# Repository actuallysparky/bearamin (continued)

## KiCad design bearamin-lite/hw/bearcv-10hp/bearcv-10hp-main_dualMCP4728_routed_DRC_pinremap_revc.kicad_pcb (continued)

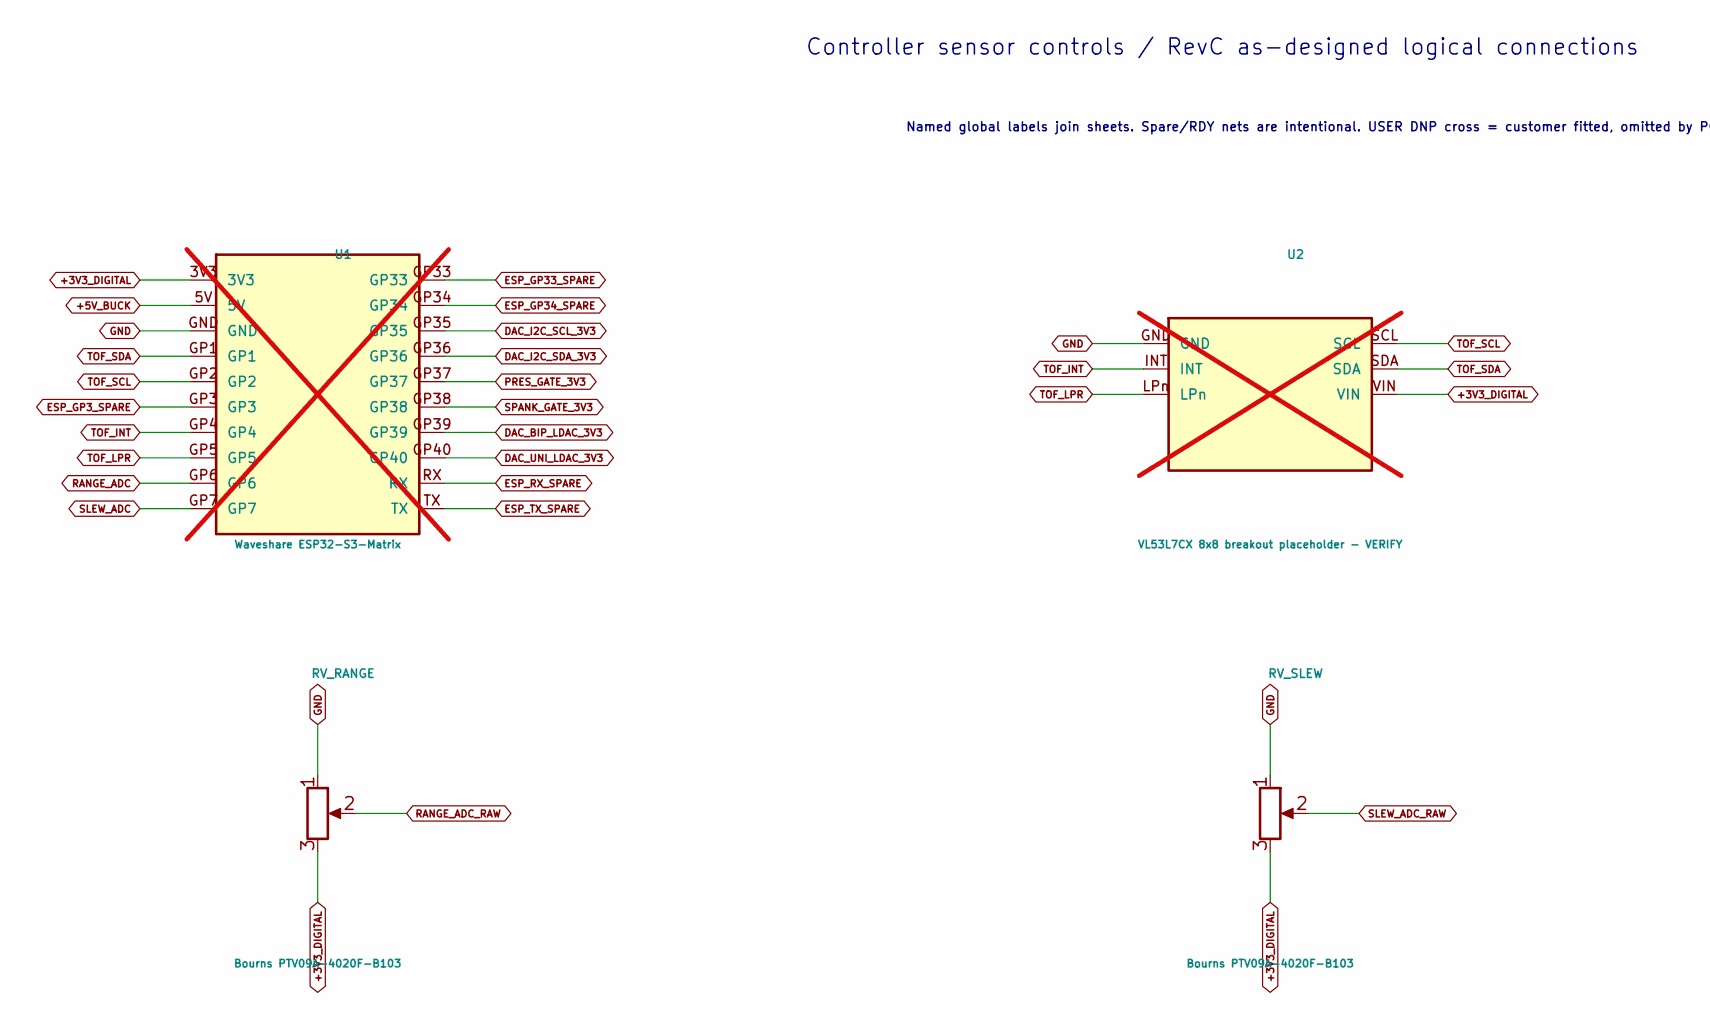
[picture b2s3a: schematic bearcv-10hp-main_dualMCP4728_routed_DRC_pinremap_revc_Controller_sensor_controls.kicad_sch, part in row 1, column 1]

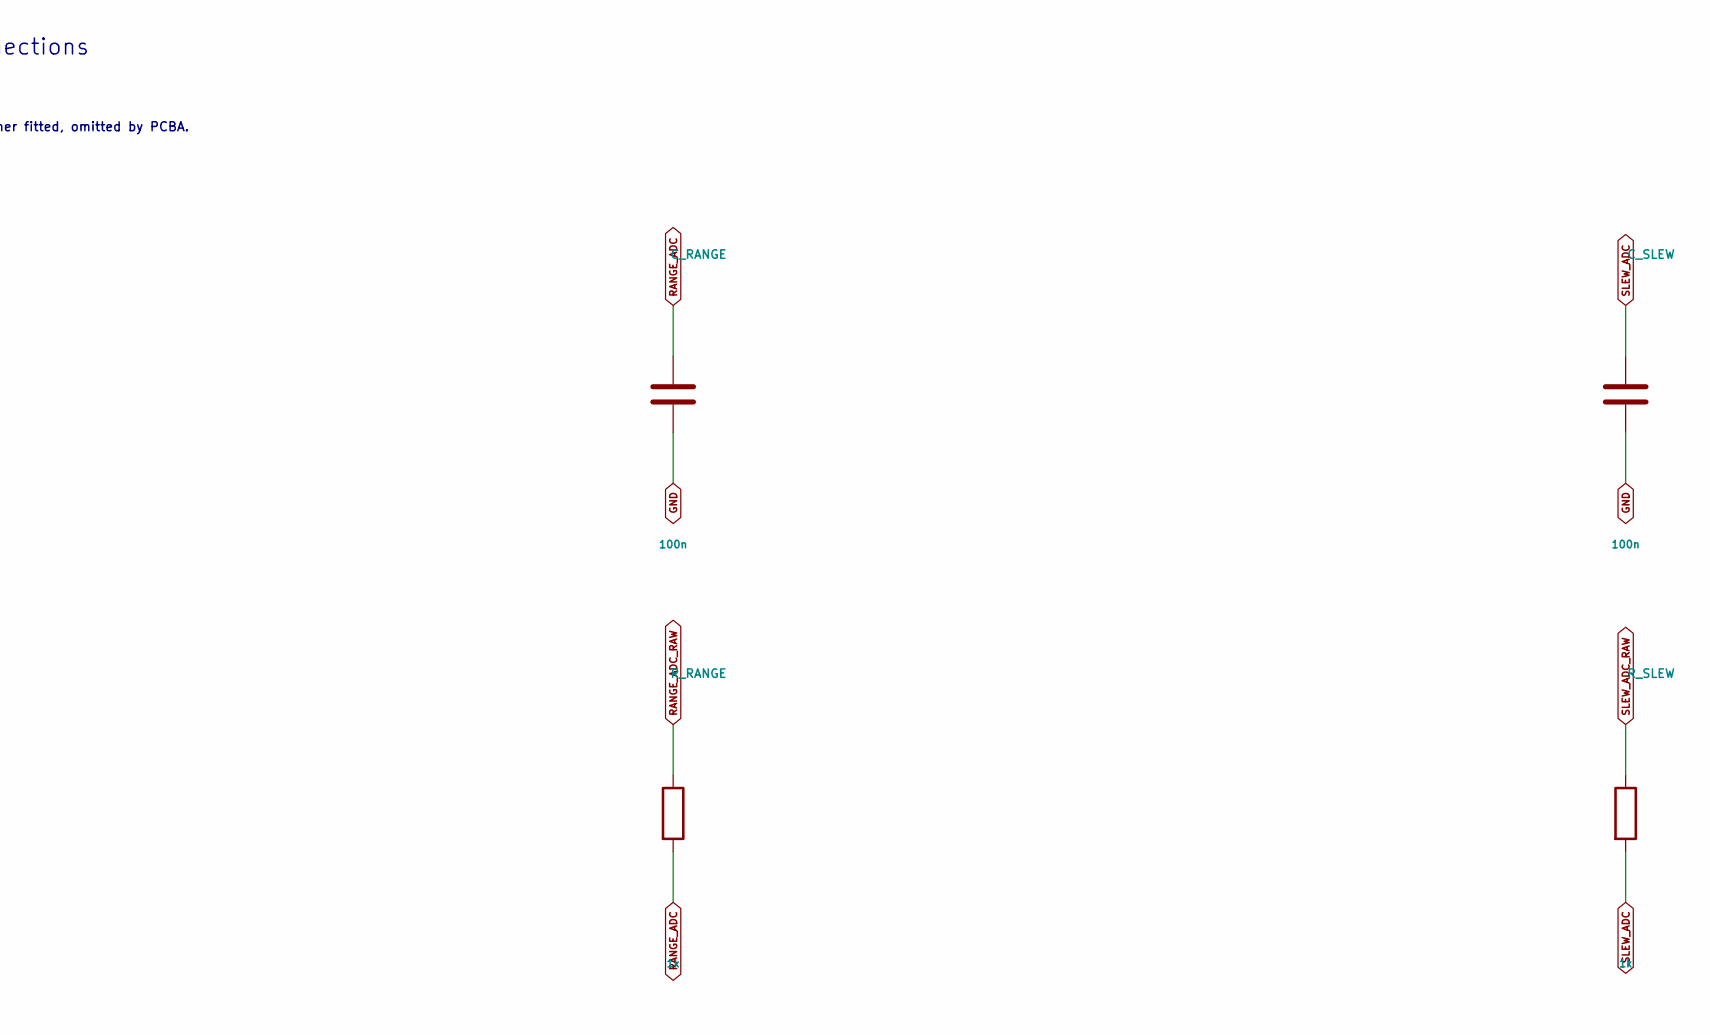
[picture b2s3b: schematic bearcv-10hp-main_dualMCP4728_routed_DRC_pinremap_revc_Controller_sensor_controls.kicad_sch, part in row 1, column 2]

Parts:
C_RANGE: 100n; MPN CC0603KRX7R9BB104; JLCPCB Part C14663
C_SLEW: 100n; MPN CC0603KRX7R9BB104; JLCPCB Part C14663
RV_RANGE: Bourns PTV09A-4020F-B103; Potentiometer_Bourns_PTV09A-4F_L20mm_Horizontal_Rear; MPN PTV09A-4020F-B103
RV_SLEW: Bourns PTV09A-4020F-B103; Potentiometer_Bourns_PTV09A-4F_L20mm_Horizontal_Rear; MPN PTV09A-4020F-B103
R_RANGE: 1k; MPN 0603WAF1001T5E; JLCPCB Part C21190
R_SLEW: 1k; MPN 0603WAF1001T5E; JLCPCB Part C21190
U1: Waveshare ESP32-S3-Matrix; MPN DNP; not fitted
U2: VL53L7CX 8x8 breakout placeholder - VERIFY; MPN DNP; not fitted

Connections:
+3V3_DIGITAL: RV_RANGE.3, RV_SLEW.3, U1.3V3, U2.VIN; also elsewhere on the board
+5V_BUCK: U1.5V; also elsewhere on the board
DAC_BIP_LDAC_3V3: U1.GP39; also elsewhere on the board
DAC_I2C_SCL_3V3: U1.GP35; also elsewhere on the board
DAC_I2C_SDA_3V3: U1.GP36; also elsewhere on the board
DAC_UNI_LDAC_3V3: U1.GP40; also elsewhere on the board
ESP_GP3_SPARE: U1.GP3
ESP_GP33_SPARE: U1.GP33
ESP_GP34_SPARE: U1.GP34
ESP_RX_SPARE: U1.RX
ESP_TX_SPARE: U1.TX
GND: C_RANGE.2, C_SLEW.2, RV_RANGE.1, RV_SLEW.1, U1.GND, U2.GND; also elsewhere on the board
PRES_GATE_3V3: U1.GP37; also elsewhere on the board
RANGE_ADC: C_RANGE.1, R_RANGE.2, U1.GP6
RANGE_ADC_RAW: RV_RANGE.2, R_RANGE.1
SLEW_ADC: C_SLEW.1, R_SLEW.2, U1.GP7
SLEW_ADC_RAW: RV_SLEW.2, R_SLEW.1
SPANK_GATE_3V3: U1.GP38; also elsewhere on the board
TOF_INT: U1.GP4, U2.INT
TOF_LPR: U1.GP5, U2.LPn
TOF_SCL: U1.GP2, U2.SCL
TOF_SDA: U1.GP1, U2.SDA

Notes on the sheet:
Controller sensor controls / RevC as-designed logical connections
Named global labels join sheets. Spare/RDY nets are intentional. USER DNP cross = customer fitted, omitted by PCBA.

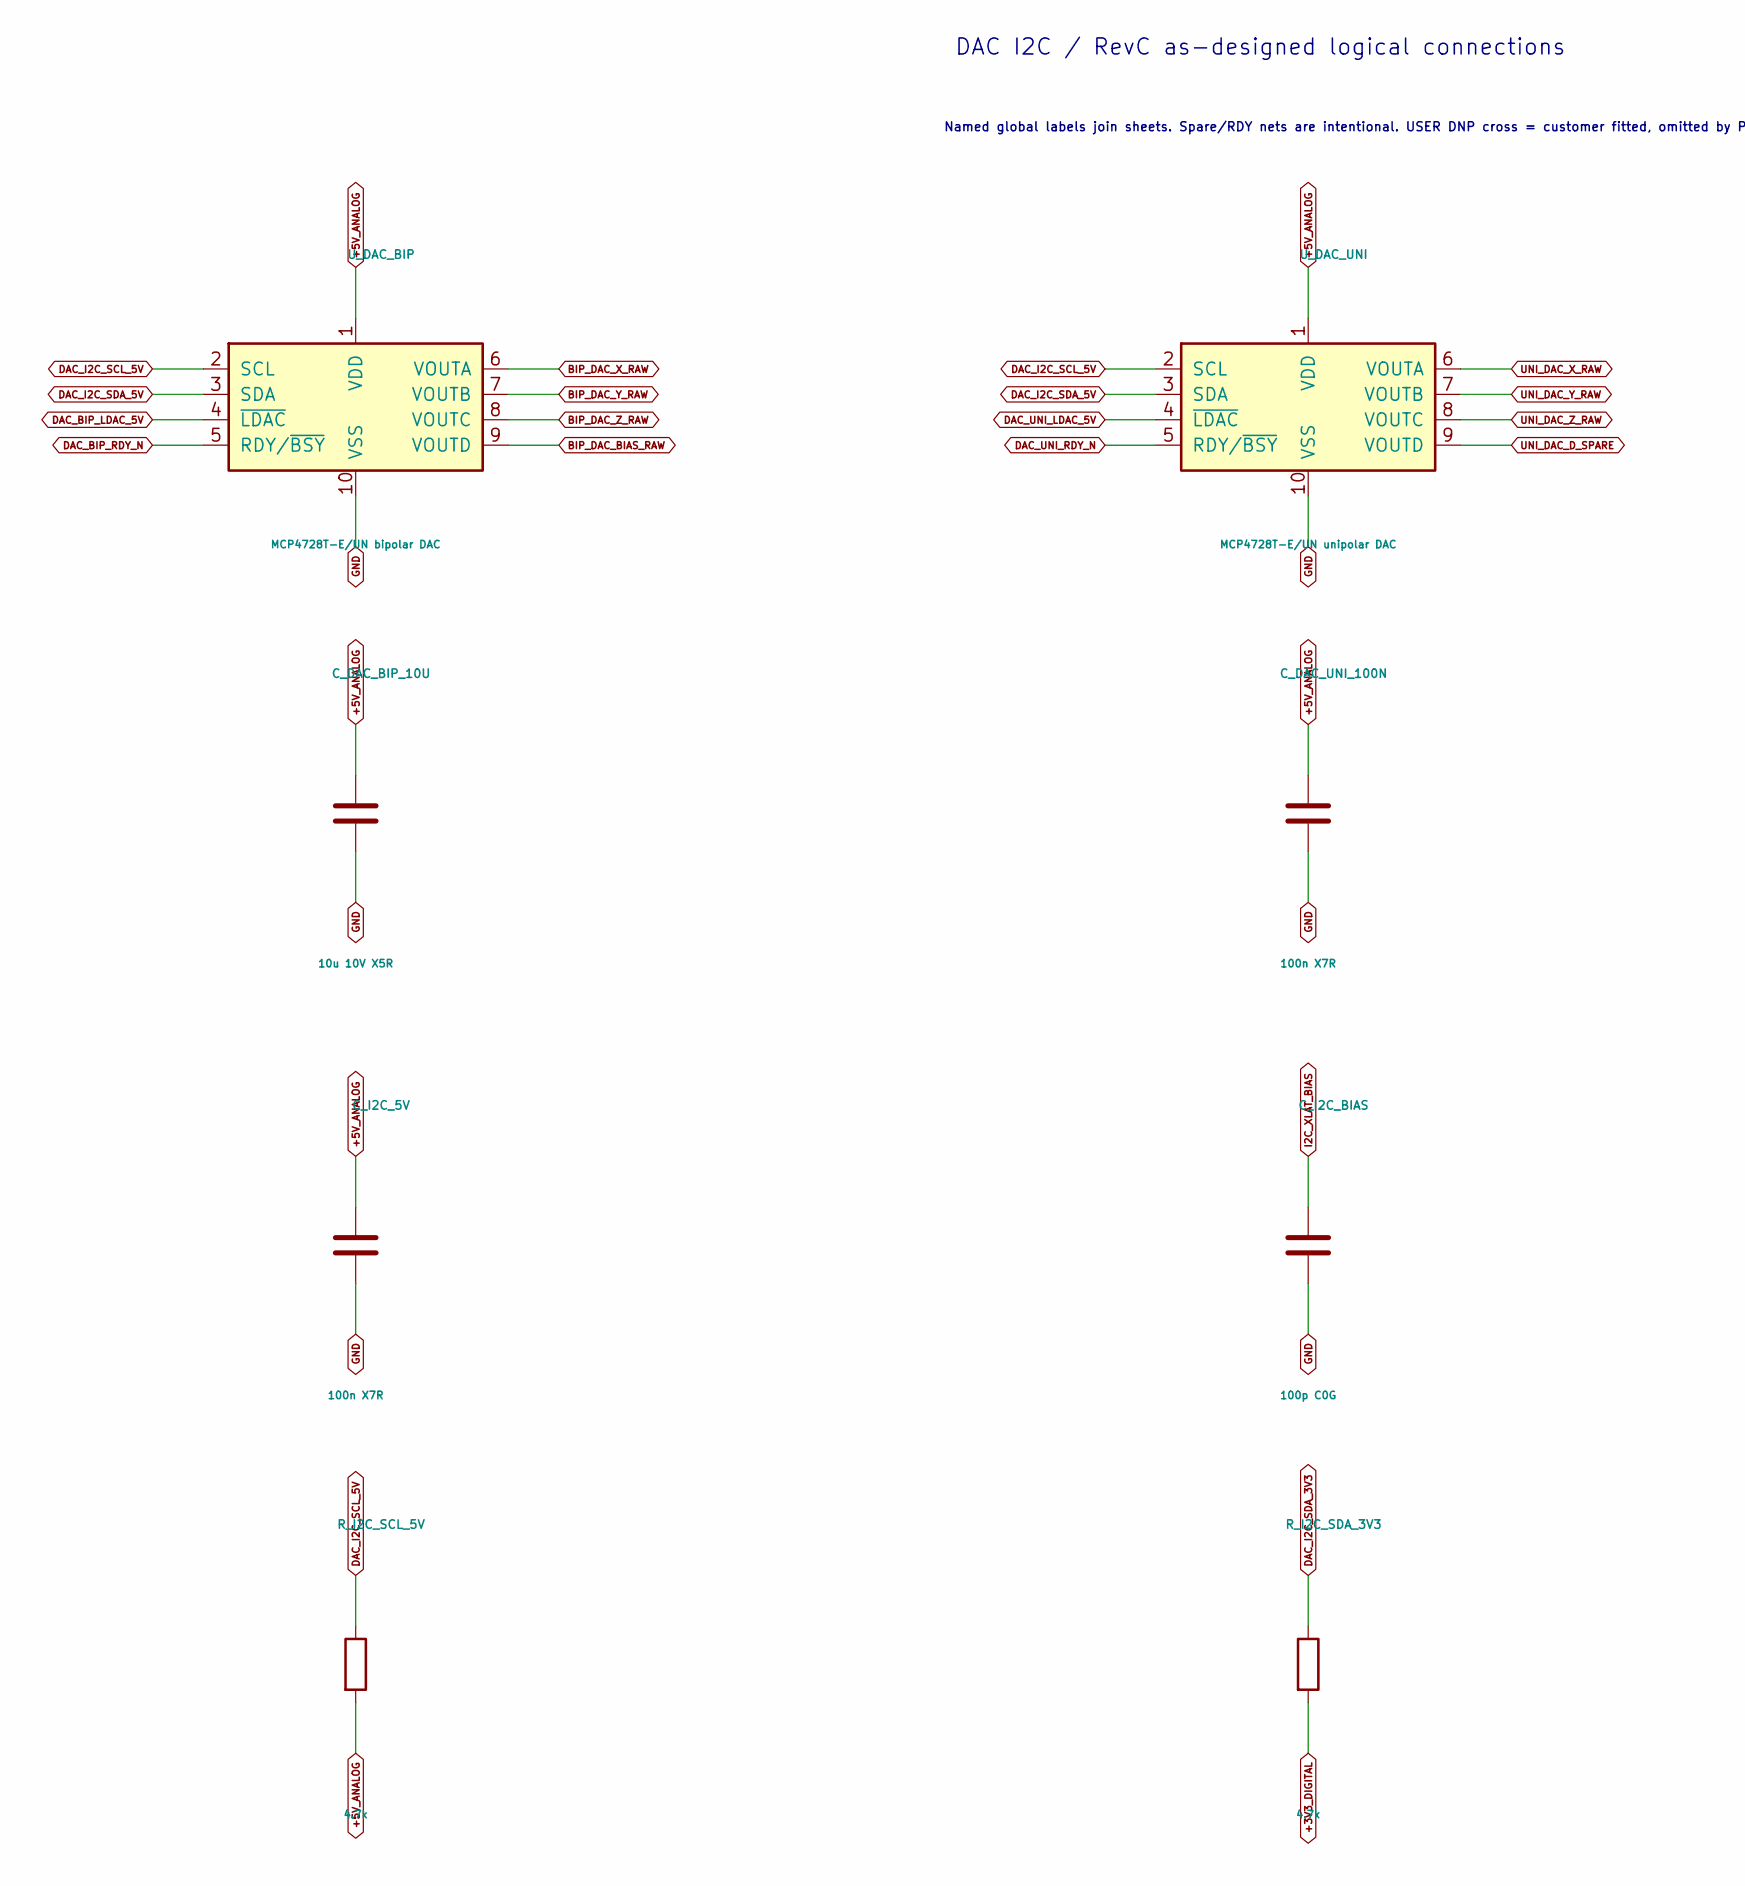
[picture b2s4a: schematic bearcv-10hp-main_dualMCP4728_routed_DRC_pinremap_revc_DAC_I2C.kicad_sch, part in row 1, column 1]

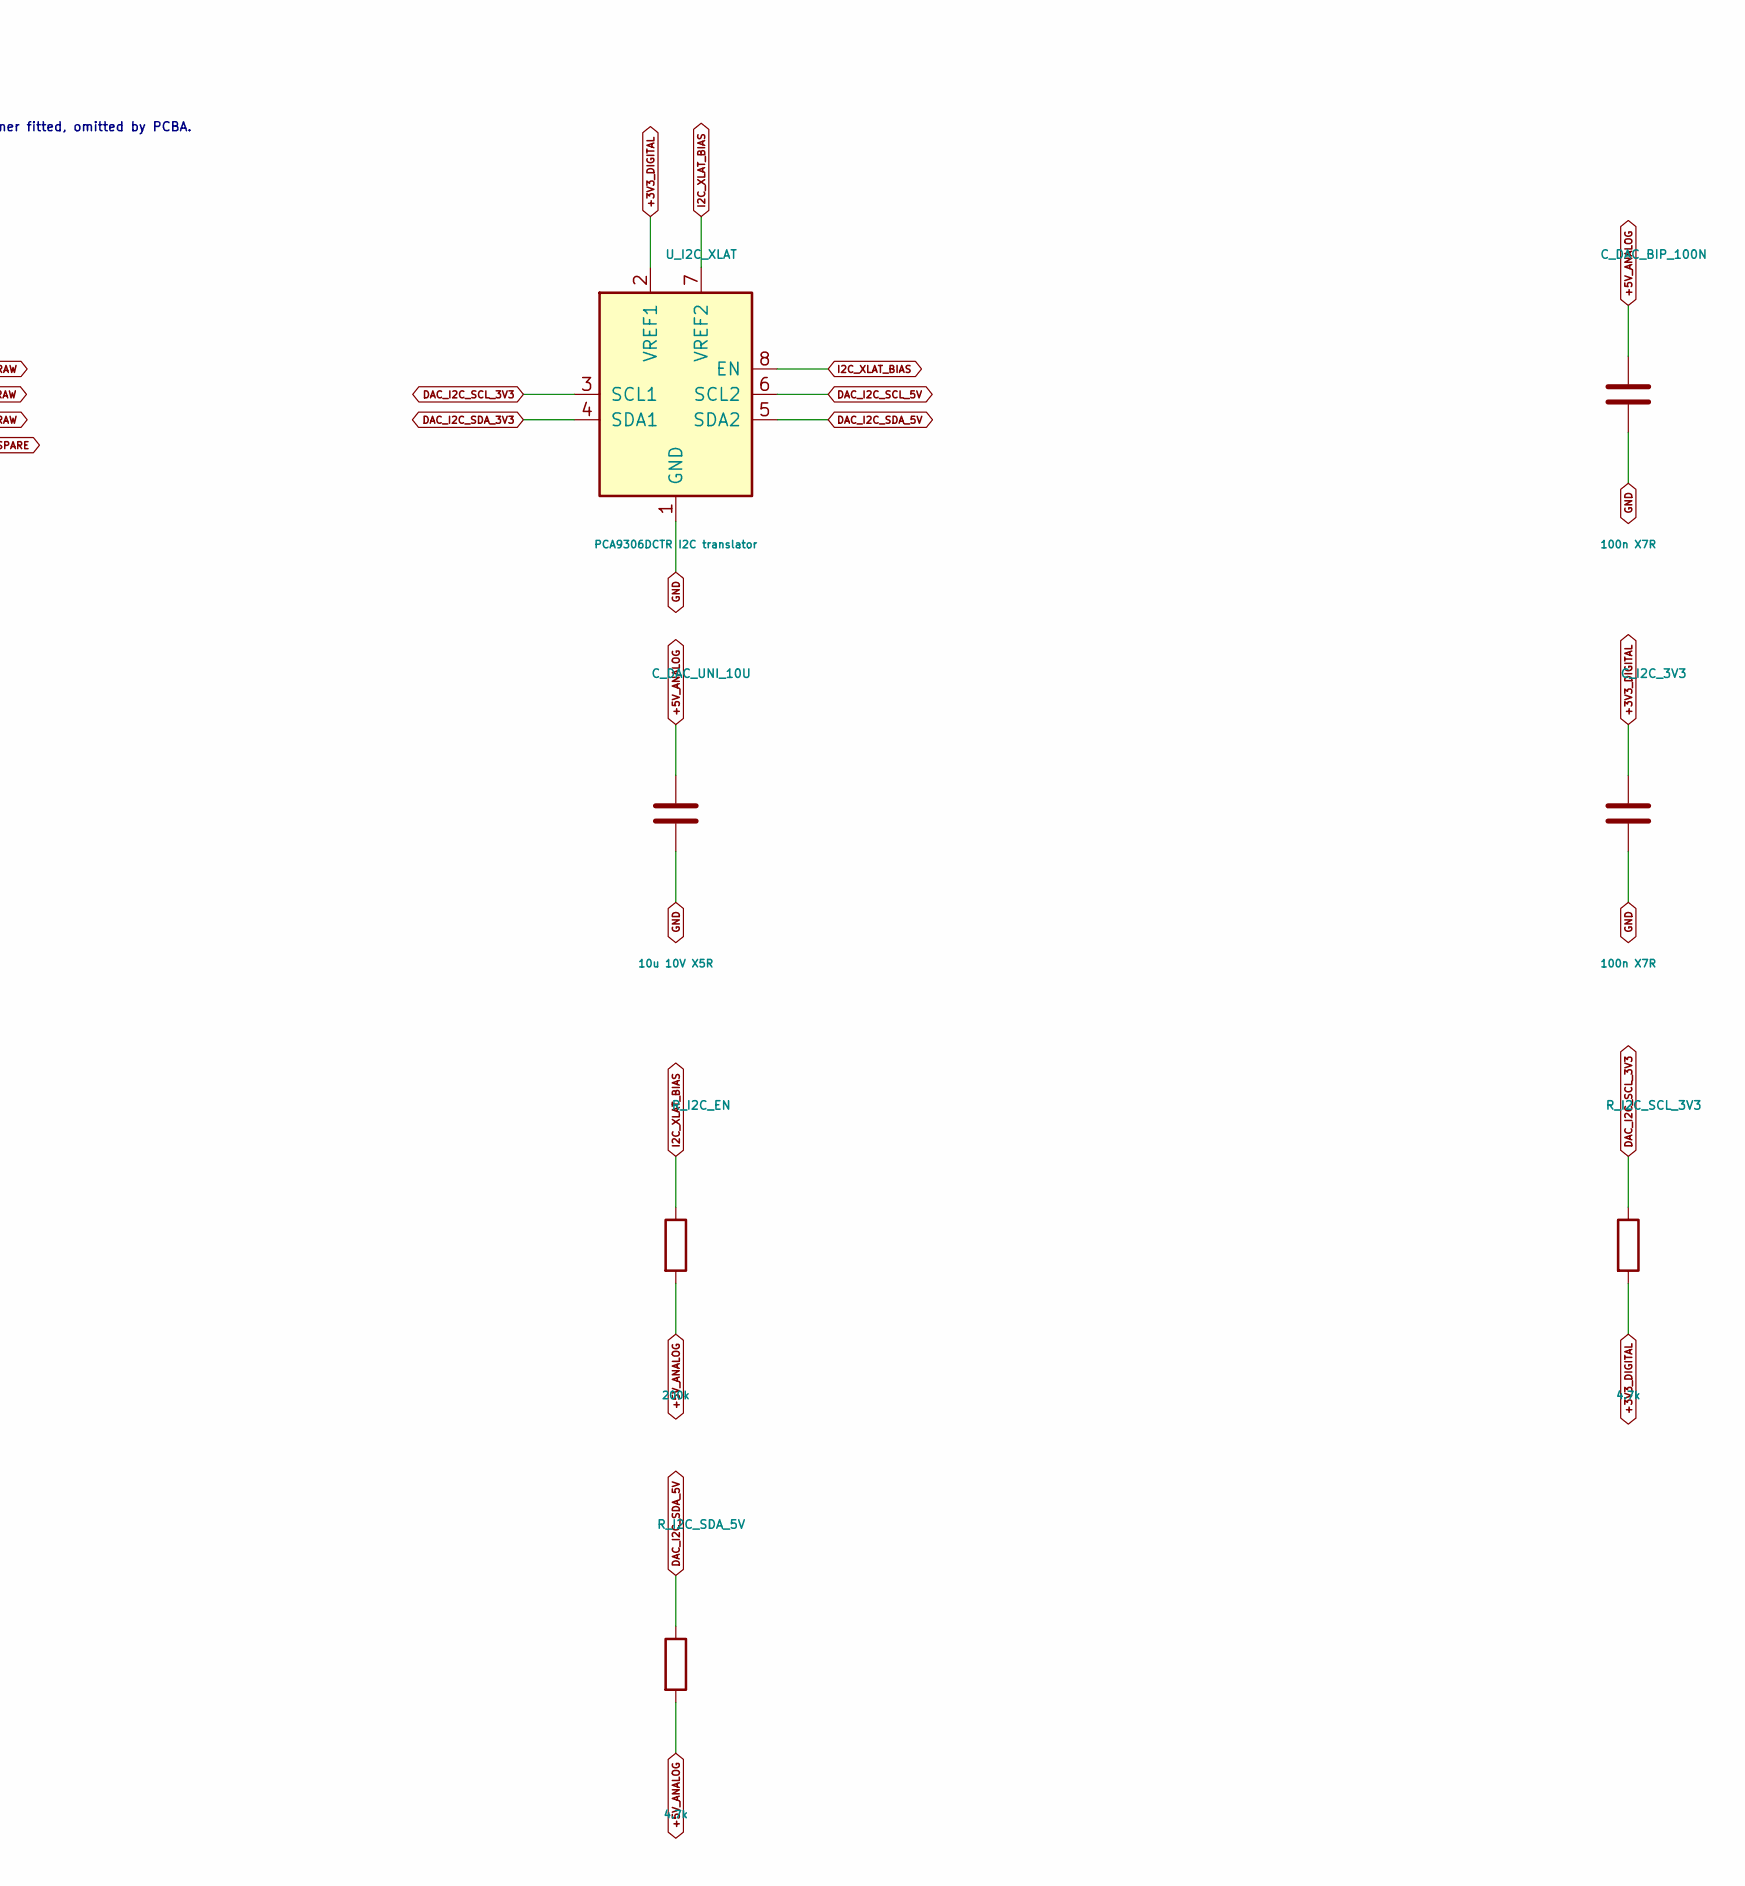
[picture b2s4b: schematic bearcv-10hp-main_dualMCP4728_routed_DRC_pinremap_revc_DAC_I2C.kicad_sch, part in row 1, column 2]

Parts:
C_DAC_BIP_10U: 10u 10V X5R; MPN CL10A106MA8NRNC; JLCPCB Part C96446
C_DAC_BIP_100N: 100n X7R; MPN CC0603KRX7R9BB104; JLCPCB Part C14663
C_DAC_UNI_10U: 10u 10V X5R; MPN CL10A106MA8NRNC; JLCPCB Part C96446
C_DAC_UNI_100N: 100n X7R; MPN CC0603KRX7R9BB104; JLCPCB Part C14663
C_I2C_3V3, C_I2C_5V: 100n X7R; MPN CC0603KRX7R9BB104; JLCPCB Part C14663
C_I2C_BIAS: 100p C0G; MPN CL10C101JB8NNNC; JLCPCB Part C14858
R_I2C_EN: 200k; MPN 0603WAF2003T5E; JLCPCB Part C25811
R_I2C_SCL_3V3, R_I2C_SCL_5V, R_I2C_SDA_3V3, R_I2C_SDA_5V: 4.7k; MPN 0603WAF4701T5E; JLCPCB Part C23162
U_DAC_BIP: MCP4728T-E/UN bipolar DAC; MPN MCP4728T-E/UN; JLCPCB Part C478093
U_DAC_UNI: MCP4728T-E/UN unipolar DAC; MPN MCP4728T-E/UN; JLCPCB Part C478093
U_I2C_XLAT: PCA9306DCTR I2C translator; MPN PCA9306DCTR; JLCPCB Part C123752

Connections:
+3V3_DIGITAL: C_I2C_3V3.1, R_I2C_SCL_3V3.2, R_I2C_SDA_3V3.2, U_I2C_XLAT.2 (VREF1); also elsewhere on the board
+5V_ANALOG: C_DAC_BIP_10U.1, C_DAC_BIP_100N.1, C_DAC_UNI_10U.1, C_DAC_UNI_100N.1, C_I2C_5V.1, R_I2C_EN.2, R_I2C_SCL_5V.2, R_I2C_SDA_5V.2, U_DAC_BIP.1 (VDD), U_DAC_UNI.1 (VDD); also elsewhere on the board
BIP_DAC_BIAS_RAW: U_DAC_BIP.9 (VOUTD); also elsewhere on the board
BIP_DAC_X_RAW: U_DAC_BIP.6 (VOUTA); also elsewhere on the board
BIP_DAC_Y_RAW: U_DAC_BIP.7 (VOUTB); also elsewhere on the board
BIP_DAC_Z_RAW: U_DAC_BIP.8 (VOUTC); also elsewhere on the board
DAC_BIP_LDAC_5V: U_DAC_BIP.4 (~LDAC); also elsewhere on the board
DAC_BIP_RDY_N: U_DAC_BIP.5 (RDY/~BSY)
DAC_I2C_SCL_3V3: R_I2C_SCL_3V3.1, U_I2C_XLAT.3 (SCL1); also elsewhere on the board
DAC_I2C_SCL_5V: R_I2C_SCL_5V.1, U_DAC_BIP.2 (SCL), U_DAC_UNI.2 (SCL), U_I2C_XLAT.6 (SCL2); also elsewhere on the board
DAC_I2C_SDA_3V3: R_I2C_SDA_3V3.1, U_I2C_XLAT.4 (SDA1); also elsewhere on the board
DAC_I2C_SDA_5V: R_I2C_SDA_5V.1, U_DAC_BIP.3 (SDA), U_DAC_UNI.3 (SDA), U_I2C_XLAT.5 (SDA2); also elsewhere on the board
DAC_UNI_LDAC_5V: U_DAC_UNI.4 (~LDAC); also elsewhere on the board
DAC_UNI_RDY_N: U_DAC_UNI.5 (RDY/~BSY)
GND: C_DAC_BIP_10U.2, C_DAC_BIP_100N.2, C_DAC_UNI_10U.2, C_DAC_UNI_100N.2, C_I2C_3V3.2, C_I2C_5V.2, C_I2C_BIAS.2, U_DAC_BIP.10 (VSS), U_DAC_UNI.10 (VSS), U_I2C_XLAT.1 (GND); also elsewhere on the board
I2C_XLAT_BIAS: C_I2C_BIAS.1, R_I2C_EN.1, U_I2C_XLAT.7 (VREF2), U_I2C_XLAT.8 (EN)
UNI_DAC_D_SPARE: U_DAC_UNI.9 (VOUTD); also elsewhere on the board
UNI_DAC_X_RAW: U_DAC_UNI.6 (VOUTA); also elsewhere on the board
UNI_DAC_Y_RAW: U_DAC_UNI.7 (VOUTB); also elsewhere on the board
UNI_DAC_Z_RAW: U_DAC_UNI.8 (VOUTC); also elsewhere on the board

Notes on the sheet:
DAC I2C / RevC as-designed logical connections
Named global labels join sheets. Spare/RDY nets are intentional. USER DNP cross = customer fitted, omitted by PCBA.

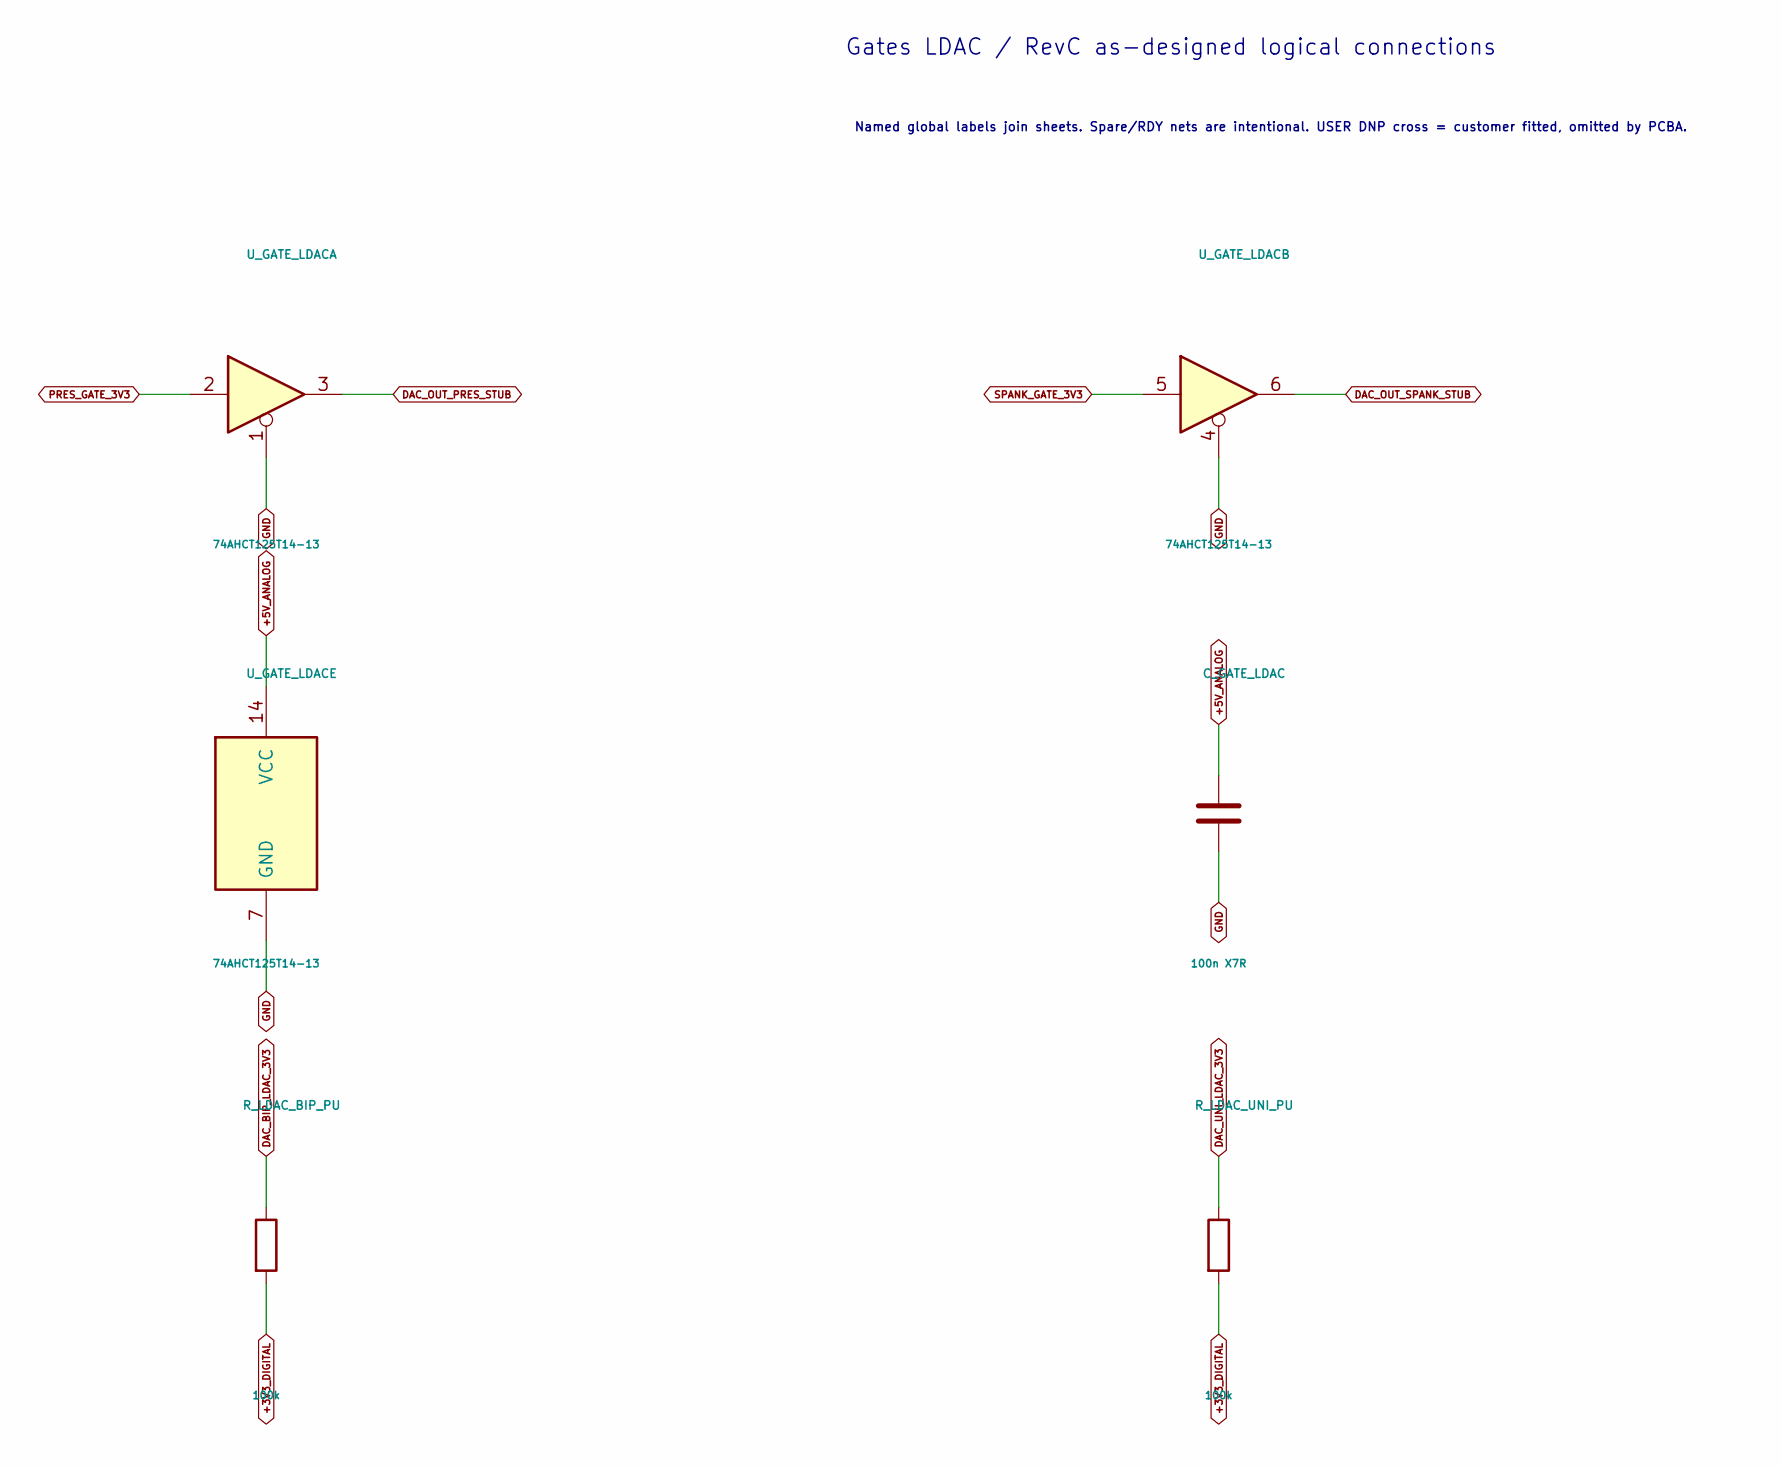
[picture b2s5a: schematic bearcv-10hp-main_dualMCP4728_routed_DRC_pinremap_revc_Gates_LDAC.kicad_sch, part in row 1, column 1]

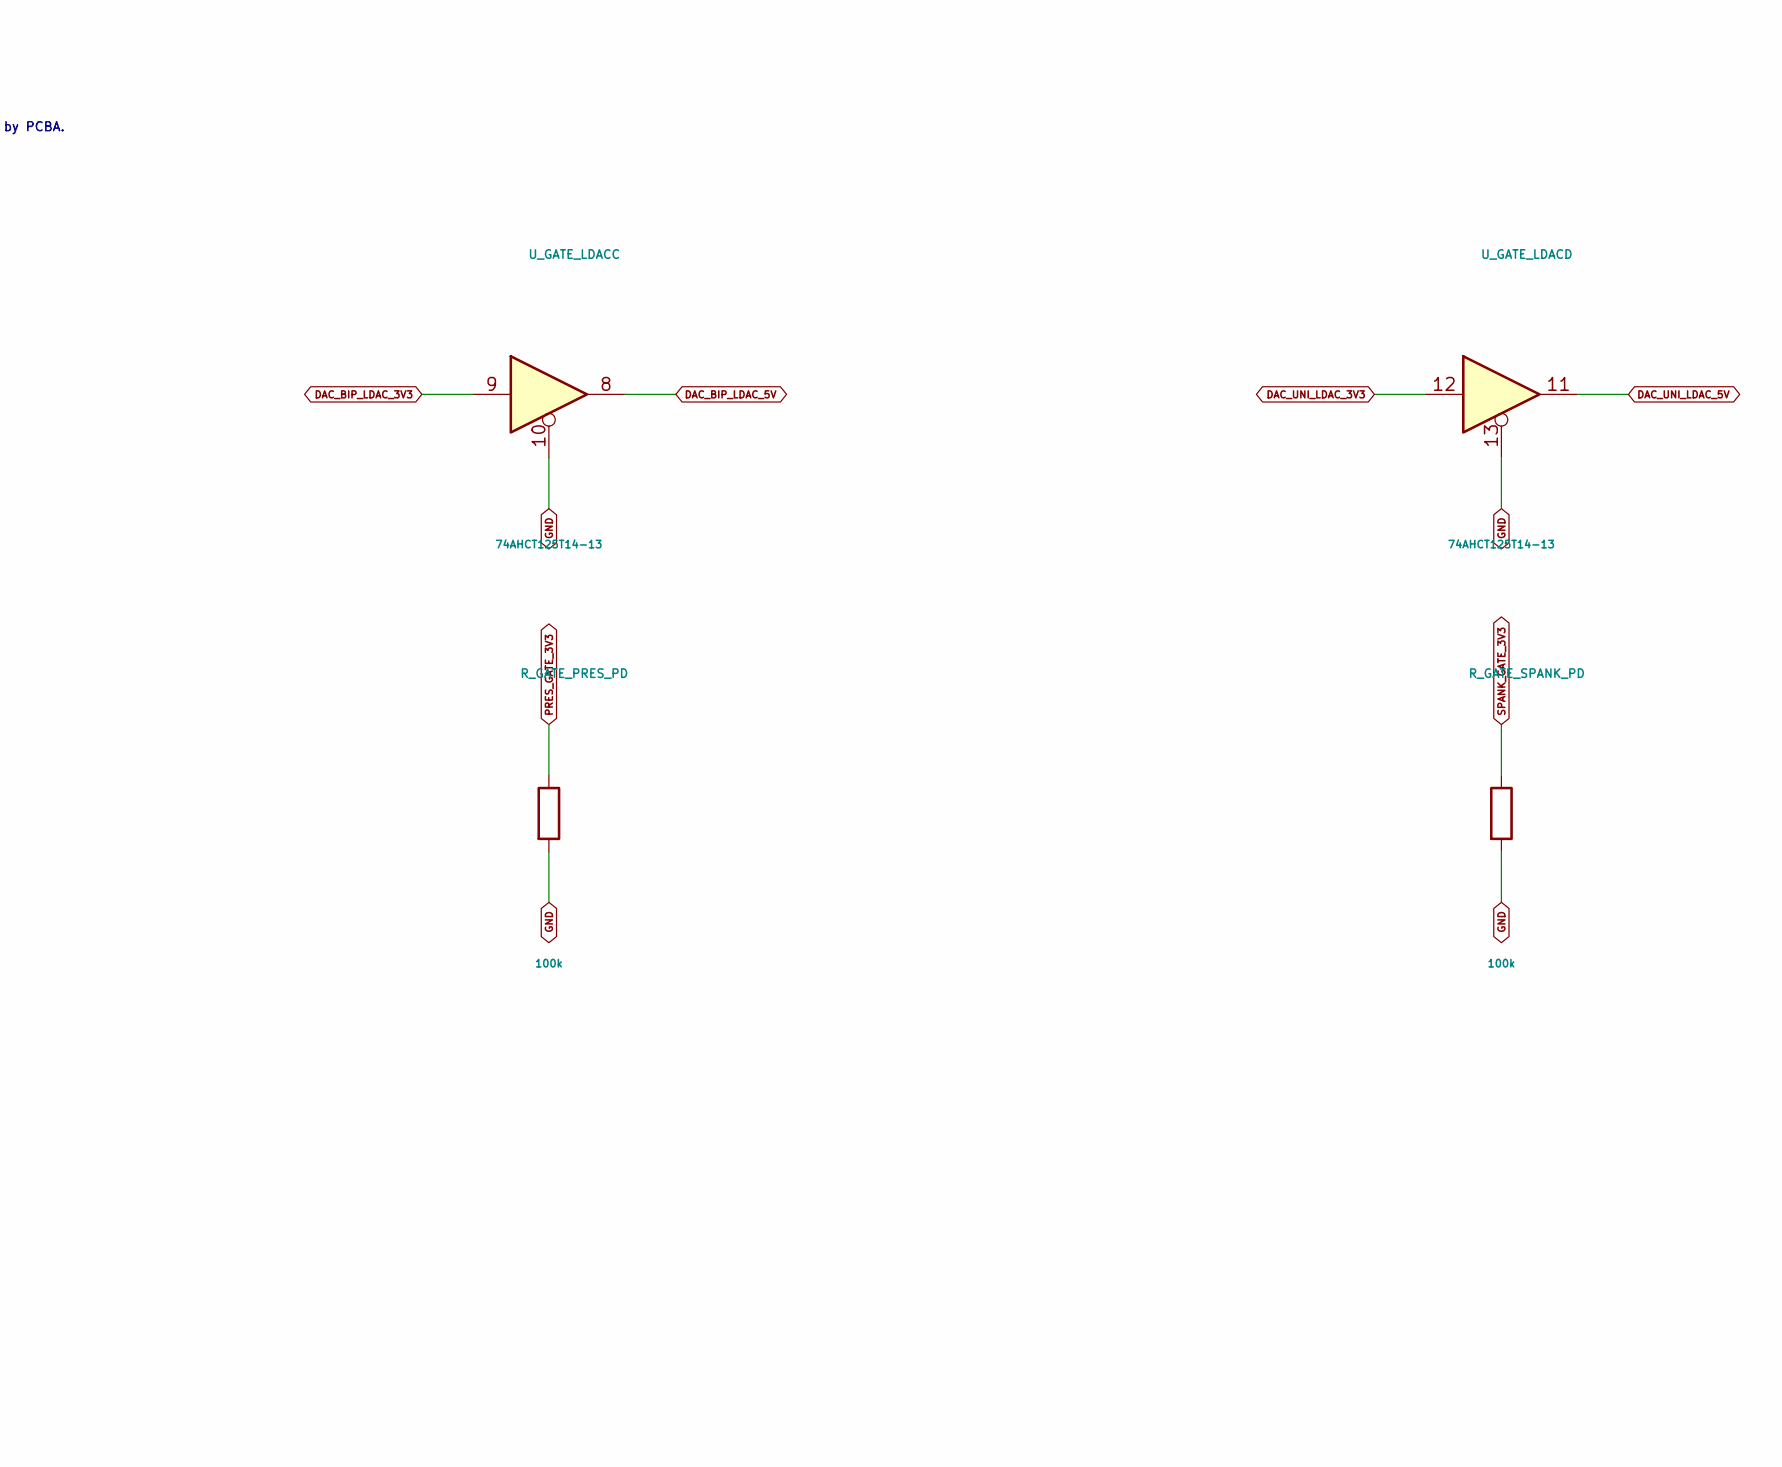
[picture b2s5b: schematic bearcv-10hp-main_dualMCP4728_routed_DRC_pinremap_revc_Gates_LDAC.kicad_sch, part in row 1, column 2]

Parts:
C_GATE_LDAC: 100n X7R; MPN CC0603KRX7R9BB104; JLCPCB Part C14663
R_GATE_PRES_PD: 100k; MPN 0603WAF1003T5E; JLCPCB Part C25803
R_GATE_SPANK_PD: 100k; MPN 0603WAF1003T5E; JLCPCB Part C25803
R_LDAC_BIP_PU: 100k; MPN 0603WAF1003T5E; JLCPCB Part C25803
R_LDAC_UNI_PU: 100k; MPN 0603WAF1003T5E; JLCPCB Part C25803
U_GATE_LDAC: 74AHCT125T14-13; MPN 74AHCT125T14-13; JLCPCB Part C176917

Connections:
+3V3_DIGITAL: R_LDAC_BIP_PU.2, R_LDAC_UNI_PU.2; also elsewhere on the board
+5V_ANALOG: C_GATE_LDAC.1, U_GATE_LDAC.14 (VCC); also elsewhere on the board
DAC_BIP_LDAC_3V3: R_LDAC_BIP_PU.1, U_GATE_LDAC.9; also elsewhere on the board
DAC_BIP_LDAC_5V: U_GATE_LDAC.8; also elsewhere on the board
DAC_OUT_PRES_STUB: U_GATE_LDAC.3; also elsewhere on the board
DAC_OUT_SPANK_STUB: U_GATE_LDAC.6; also elsewhere on the board
DAC_UNI_LDAC_3V3: R_LDAC_UNI_PU.1, U_GATE_LDAC.12; also elsewhere on the board
DAC_UNI_LDAC_5V: U_GATE_LDAC.11; also elsewhere on the board
GND: C_GATE_LDAC.2, R_GATE_PRES_PD.2, R_GATE_SPANK_PD.2, U_GATE_LDAC.1, U_GATE_LDAC.4, U_GATE_LDAC.7 (GND), U_GATE_LDAC.10, U_GATE_LDAC.13; also elsewhere on the board
PRES_GATE_3V3: R_GATE_PRES_PD.1, U_GATE_LDAC.2; also elsewhere on the board
SPANK_GATE_3V3: R_GATE_SPANK_PD.1, U_GATE_LDAC.5; also elsewhere on the board

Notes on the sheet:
Gates LDAC / RevC as-designed logical connections
Named global labels join sheets. Spare/RDY nets are intentional. USER DNP cross = customer fitted, omitted by PCBA.
